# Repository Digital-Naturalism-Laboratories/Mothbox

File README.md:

# Mothbox
Developing an open source,low cost automated system for Moth-Lighting photography 

look at the wiki for up to date information on assembly and usage
https://github.com/Digital-Naturalism-Laboratories/Mothbox/wiki

It's a compact, low cost device you can get running with simple modifications of off-the-shelf parts! And no soldering really needed!

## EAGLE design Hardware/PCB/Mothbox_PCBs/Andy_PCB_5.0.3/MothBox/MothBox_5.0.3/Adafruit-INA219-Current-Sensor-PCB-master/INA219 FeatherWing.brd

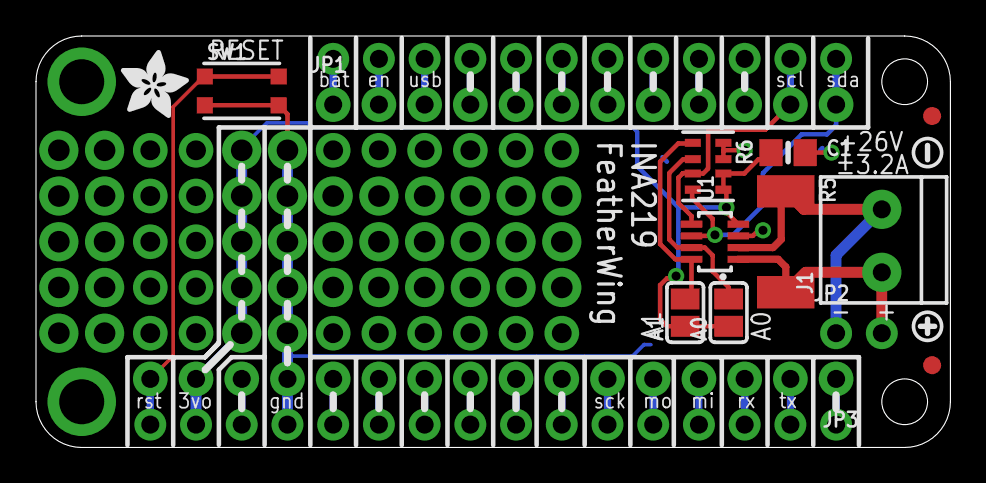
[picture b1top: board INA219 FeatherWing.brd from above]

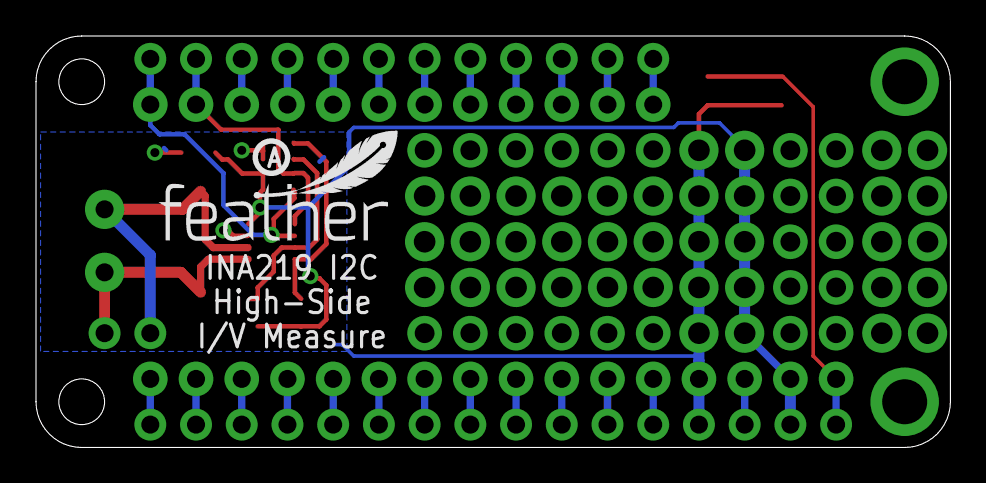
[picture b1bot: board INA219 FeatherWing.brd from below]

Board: 2 copper layers, 50.8 x 22.9 mm, 19 parts (2 on the bottom side), 32 nets.

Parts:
A0, A1: SOLDERJUMPER_REFLOW_NOPASTE
C1: 1uF; 0805-NO@1
FID1, FID2: FIDUCIAL_1MM
J1: 3.5mm; TERMBLOCK_1X2-3.5MM
JP1: 1X12_ROUND_76MIL
JP2: 1X02_ROUND
JP3: 1X16_ROUND_76MIL
MS1: FEATHERWING
R5: 0.1/1% (PT2512FK-070R1L); 2512
R6: 10K; RESPACK_4X0603
SW1: KMR2; BTN_KMR2_4.6X2.8
U1: INA219BIDCNT; SOT23-8
U$12: SYMBOL_PLUS
U$13: SYMBOL_MINUS
U$15: FEATHERLOGO_SMALL
U$16: ADAFRUIT_3.5MM
U$17: PCBFEAT-REV-040

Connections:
3.3V: A0.1, A1.1, C1.1, JP3.15, MS1.2, R6.5, R6.6, U1.4
A: JP3.12, MS1.5
AREF: JP3.14, MS1.3
B: JP3.11, MS1.6
C: JP3.10, MS1.7
D: JP3.9, MS1.8
E: JP3.8, MS1.9
EN: JP1.2, MS1.27
F: JP3.7, MS1.10
G: JP3.1, MS1.16
GND: C1.2, JP3.13, MS1.4, R6.7, R6.8, SW1.B, SW1.B', U1.3
H: JP1.10, MS1.19
I: JP1.9, MS1.20
J: JP1.8, MS1.21
K: JP1.7, MS1.22
L: JP1.6, MS1.23
M: JP1.5, MS1.24
MISO: JP3.4, MS1.13
MOSI: JP3.5, MS1.12
N: JP1.4, MS1.25
unnamed: A1.2, R6.1, U1.8
unnamed: A0.2, R6.2, U1.7
RESET: JP3.16, MS1.1, SW1.A, SW1.A'
RX: JP3.3, MS1.14
SCK: JP3.6, MS1.11
SCL: JP1.11, MS1.18, R6.3, U1.5
SDA: JP1.12, MS1.17, R6.4, U1.6
TX: JP3.2, MS1.15
USB: JP1.3, MS1.26
VBAT: JP1.1, MS1.28
VIN+: J1.2, JP2.2, R5.2, U1.1
VIN-: J1.1, JP2.1, R5.1, U1.2

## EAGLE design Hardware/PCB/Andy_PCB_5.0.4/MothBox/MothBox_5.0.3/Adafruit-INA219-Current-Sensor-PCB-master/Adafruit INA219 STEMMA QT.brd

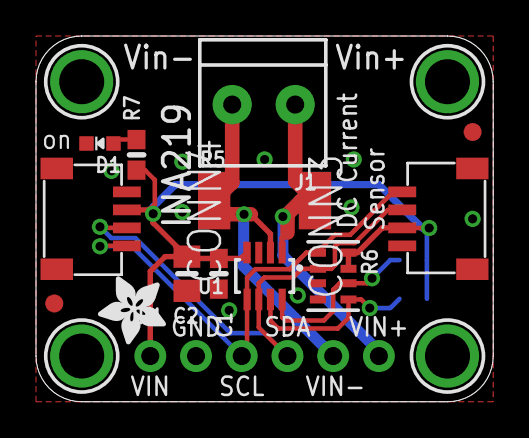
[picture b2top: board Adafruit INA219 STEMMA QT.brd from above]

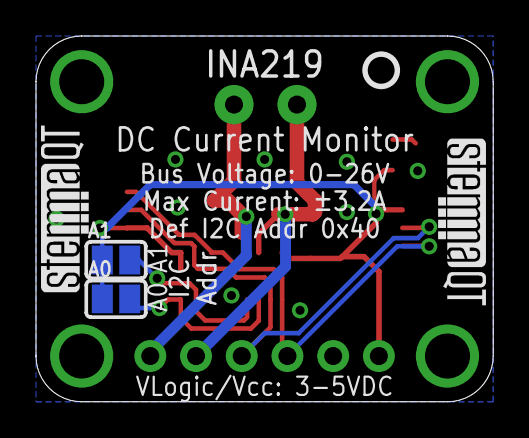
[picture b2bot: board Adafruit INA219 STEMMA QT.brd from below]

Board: 2 copper layers, 25.4 x 20.3 mm, 23 parts (5 on the bottom side), 9 nets.

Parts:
A0, A1: SOLDERJUMPER_REFLOW_NOPASTE
C1: 0.1µF; 0603-NO
C2: 10uF; 0805-NO
CONN3, CONN4: STEMMA_I2C_QT; JST_SH4
D1: GREEN; CHIPLED_0603_NOOUTLINE
FID3, FID4: FIDUCIAL_1MM
J1: 3.5mm; TERMBLOCK_1X2-3.5MM
JP1: 1X06_ROUND_70
R5: 0.1/1% (PT2512FK-070R1L); 2512
R6: 10K; RESPACK_4X0603
R7: 10K; 0603-NO
U1: INA219BIDCNT; SOT23-8
U$20, U$21, U$25, U$27: MOUNTINGHOLE2.5; MOUNTINGHOLE_2.5_PLATED
U$29: ADAFRUIT_3.5MM
U$30: PCBFEAT-REV-040
U$31, U$32: STEMMAQT

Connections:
ADDR0: A0.2, R6.5, U1.7
ADDR1: A1.2, R6.6, U1.8
GND: C1.2, C2.2, CONN3.1, CONN3.MT1, CONN3.MT2, CONN4.1, CONN4.MT1, CONN4.MT2, D1.C, JP1.2, R6.3, R6.4, U1.3
unnamed: D1.A, R7.2
SCL: CONN3.4, CONN4.4, JP1.3, R6.1, U1.5
SDA: CONN3.3, CONN4.3, JP1.4, R6.2, U1.6
VCC: A0.1, A1.1, C1.1, C2.1, CONN3.2, CONN4.2, JP1.1, R6.7, R6.8, R7.1, U1.4
VIN+: J1.2, JP1.6, R5.2, U1.1
VIN-: J1.1, JP1.5, R5.1, U1.2

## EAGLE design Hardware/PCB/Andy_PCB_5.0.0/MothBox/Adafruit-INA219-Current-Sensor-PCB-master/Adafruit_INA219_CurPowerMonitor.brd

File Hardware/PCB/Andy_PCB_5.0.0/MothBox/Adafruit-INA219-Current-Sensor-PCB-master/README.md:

## Adafruit INA219 Current Sensor PCB

<a href="http://www.adafruit.com/products/904"><br/>
Click here to purchase one from the Adafruit shop</a>
<a href="http://www.adafruit.com/products/3650"><br/>
Click here to purchase one from the Adafruit shop</a>

PCB files for the Adafruit INA219 Current Sensor. 

Format is EagleCAD schematic and board layout
* https://www.adafruit.com/product/904
* https://www.adafruit.com/product/3650

### Description

The INA219 will solve all your power-monitoring problems. Instead of struggling with two multimeters, you can just use the handy INA219B chip to both measure both the high side voltage and DC current draw over I2C with 1% precision.

Most current-measuring devices such as our current panel meter are only good for low side measuring. That means that unless you want to get a battery involved, you have to stick the measurement resistor between the target ground and true ground. This can cause problems with circuits since electronics tend to not like it when the ground references change and move with varying current draw. This chip is much smarter - it can handle high side current measuring, up to +26VDC, even though it is powered with 3 or 5V. It will also report back that high side voltage, which is great for tracking battery life or solar panels.

A precision amplifier measures the voltage across the 0.1 ohm, 1% sense resistor. Since the amplifier maximum input difference is ±320mV this means it can measure up to ±3.2 Amps. With the internal 12 bit ADC, the resolution at ±3.2A range is 0.8mA. With the internal gain set at the minimum of div8, the max current is ±400mA and the resolution is 0.1mA. Advanced hackers can remove the 0.1 ohm current sense resistor and replace it with their own to change the range (say a 0.01 ohm to measure up 32 Amps with a resolution of 8mA)

### License

Adafruit invests time and resources providing this open source design, please support Adafruit and open-source hardware by purchasing products from [Adafruit](https://www.adafruit.com)!

Designed by Limor Fried/Ladyada for Adafruit Industries.

Creative Commons Attribution/Share-Alike, all text above must be included in any redistribution. 
See license.txt for additional details.

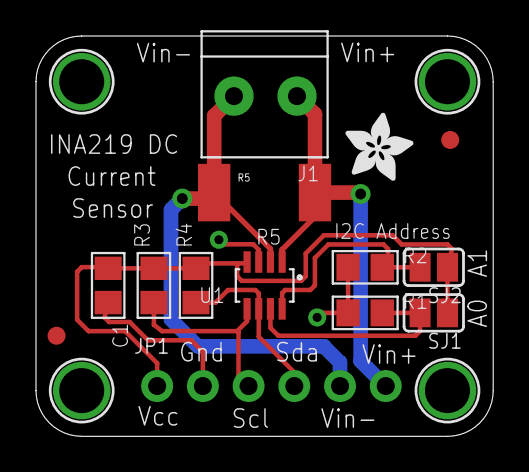
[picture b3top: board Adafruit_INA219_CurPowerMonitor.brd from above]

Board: 2 copper layers, 25.4 x 22.2 mm, 18 parts (0 on the bottom side), 8 nets.

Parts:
C1: 0.1µF; 0805
FID1, FID2: FIDUCIAL""; FIDUCIAL_1MM
J1: TERMBLOCK_1X2-3.5MM; 1X2-3.5MM
JP1: 1X06_ROUND_70
R1, R2, R3, R4: 10K; 0805
R5: 0.1/1% (PT2512FK-070R1L); 2512
SJ1, SJ2: SOLDERJUMPER_REFLOW_NOPASTE
U1: INA219BIDCNT; SOT23-8
U$7, U$8, U$9, U$10: MOUNTINGHOLE2.5; MOUNTINGHOLE_2.5_PLATED
U$11: ADAFRUIT_3.5MM

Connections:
GND: C1.2, JP1.2, R1.1, R2.1, U1.3
unnamed: R2.2, SJ2.2, U1.8
unnamed: R1.2, SJ1.2, U1.7
SCL: JP1.3, R3.1, U1.5
SDA: JP1.4, R4.1, U1.6
VCC: C1.1, JP1.1, R3.2, R4.2, SJ1.1, SJ2.1, U1.4
VIN+: J1.2, JP1.6, R5.2, U1.1
VIN-: J1.1, JP1.5, R5.1, U1.2

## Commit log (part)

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2025-11-27 Had to swap SW2 for a SMD version
2025-12-04 Add BeetlePalooza-related links
    include Imageomics URL and Bucket of Bugs project repo
2025-12-16 organizing site
2025-12-16 External parts
2025-12-16 fix names
2025-12-17 Define styles for navigation list levels
    Added styles for nested navigation levels.
2025-12-17 Update custom.scss with active link style
    Commented out font-weight property and added active link background style.
2025-12-17 Fix SCSS syntax and update background properties
2025-12-17 Update nav-list-link selector to use anchor tag
2025-12-17 Add width property to Level 2 nav-list links
2025-12-17 Adjust margin-left for nav-list links
    Updated margin-left for nav-list links from 1rem to 2rem.
2025-12-20 Organizing Case Options
2025-12-23 v5.0.4 schematic and PCB done. Ready for review
2025-12-24 flushing old versions
2025-12-26 renamed 24v areas to be actually 9-36v areas
2025-12-26 update kicad
2025-12-27 updated 5.x case stuff with rubber ties
2025-12-28 MADE UV m3 holes ready for JLCPCB
2025-12-29 updated footprints of d1 d2 d4 to SOD 123
2026-01-06 new Display for 4.x
    Refactor GPIO connection checks and update display logic. Added mode descriptions and improved voltage percentage calculation.
2026-01-06 Update controls.txt with new configuration values
2026-01-06 Add photo counting and update display info
2026-01-06 4.16.4 stuff
2026-01-07 Refactor shutdown process and remove GPS check
    Removed unnecessary GPS check at shutdown and updated shutdown procedure for Raspberry Pi 5.
2026-01-08 better battery values
2026-01-08 new 4.5 version cached
2026-01-08 Enhance Mothbox section with links and fixes
    Updated Mothbox descriptions with links and corrected typos.
2026-01-08 Add PCB attachment instructions to assembleincase.md
    Added instructions for attaching the PCB to the chassis with images.
2026-01-08 Add image to case_print.md
    Added an image of the 3D printable case for Mothbox.
2026-01-08 Enhance case_print.md with printing and assembly details
    Added detailed printing instructions and material list for case parts.
2026-01-09 Refactor Mothbox display logic and mode handling
    Updated mode handling and display information for Mothbox. Enhanced font usage and improved external drive information display.
2026-01-10 Adjust font sizes and layout in UpdateDisplay.py
2026-01-10 Refactor Mothbox display logic and font styles
    Refactor Mothbox display code to improve readability and update font styles. Adjusted control value retrieval and display elements for better clarity.
2026-01-13 getting rid of Pijuice only, turn everything off scripts
2026-01-17 Document Mothbeam connection setup and configuration
    Added detailed instructions for connecting Mothbeams to the mainboard, including configuration options and reinforcement tips.
2026-01-17 Update parts list for Mothbox Pro build
    Added detailed list of parts required to build a Mothbox Pro, including descriptions and prices.
2026-01-17 Update Mothbox Pro parts documentation
    Added an image and updated parts list for Mothbox Pro.
2026-01-18 added lip to front lid to hold it on better!
2026-01-19 made plug for box holes
2026-01-20 Update battery.md with regulator connection details
    Added instructions for connecting the regulator and battery power to the board.
2026-01-20 Update battery.md with setup instructions and notes
    Added notes on battery charging and Mothbox setup.
2026-01-20 Update assembly instructions for Mothbox Pro
    Added instructions for housing the Mothbox Pro and securing the PCB.
2026-01-20 Update case assembly instructions and component list
    Added DC barrel sockets to the list of components and clarified gasket usage for the back lid. Updated assembly instructions for the front acrylic and back lid.
2026-01-21 Update arms.md with assembly instructions
    Added sections on peeling plastic and attaching arms with various methods.
2026-01-22 code from 4.16.5
2026-01-22 MB Pro Scripts
2026-01-30 pro 5.1.0 firmware
2026-01-30 Finished fixing up Firmware for 4.17.0
2026-02-02 4.17.0 image files
2026-02-05 Fix broken link in processingsoftware.md
2026-02-05 Fix two broken links in cluster.md
2026-02-06 Clarify weekday and hour configuration in CSV
    Updated weekday and hour settings for clarity.
2026-02-07 Enhance battery.md with assembly and setup notes
    Added notes for battery assembly and setup steps.
2026-02-07 Expand timezone list with additional entries
    Added numerous time zones to the timezone list, expanding coverage for various regions.
2026-02-07 Revise time setting instructions for mothbox
    Updated the section on setting the time for the mothbox, including instructions for both manual and automatic time settings. Added images and clarified the process for users without internet access.
2026-02-07 Add optional custom mothbox name setup instructions
    Added instructions for setting a custom mothbox name.
2026-02-07 Update test.md with testing and battery info
    Added testing instructions and battery connection warnings.
2026-02-07 moved solar info
2026-02-07 Update get_utc_offset_hours to return rounded float
    Change return type of UTC offset to rounded float for fractional timezones.
2026-02-07 Update devblog with February 2026 entry
    Added a new entry detailing preparations for mothboxes and a bug fix related to fractional timezones.
2026-02-07 updated 5.1.1 mb image
2026-02-08 Fixed scheduling bug in 5.1.1 and 4.17.1
2026-02-08 Document Mothbox modes and settings
    Added detailed descriptions of Mothbox modes and how to set them for both DIY and Pro versions.
2026-02-08 latest case designs
2026-02-11 Fix typo in initialsetup.md
2026-02-12 fixed regex in detect as well
2026-02-12 Replace old image with new Mothbox Pro image
2026-02-12 Add connectors section to parts documentation
    Added section on connectors with options for securing the lid and legs.
2026-02-13 Update connect.md with Pi and camera connection details
    Added instructions for connecting the Pi and camera, including RTC battery installation and cable management.
2026-02-17 fixed regex
2026-02-17 Update nav_order for Classification documentation
2026-02-17 Update nav_order for Process documentation
2026-02-19 Revise project updates and add repository links
    Updated README to reflect project re-organization and added links to separate repositories.
2026-02-19 moved PCBS
2026-03-03 Add images to processing documentation
2026-03-17 Enhance instructions for connecting brown cable
    Added notes for connecting the brown cable to the camera.
2026-03-17 tweaks to forms examples
2026-03-17 scooting
2026-03-17 Update metadata logging and deployment instructions
    Revised instructions for metadata logging and Mothbox operation.
2026-03-17 Update usage instructions for Mothbox deployment
2026-03-18 Enhance battery charging and deployment instructions
    Added a warning about charging batteries before first use and improved instructions for preparing and deploying the Mothbox.
2026-03-18 Update databases.md with transition notice to Classify
    Added a note about the transition to the new Classify software.
2026-03-19 Update filament suggestions with outdoor usage notes
    Added a note about the suitability of regular PETG for outdoor equipment and cautioned against using PLA in tropical conditions.
2026-03-24 Update case_print.md with additional acrylic details
2026-03-24 Revise Mothbox DIY guide title and content
    Updated the title and added an introductory paragraph with an image for the Mothbox DIY guide.
2026-03-26 Remove FTP credentials from RemoveAccents_FTP.py
    Removed sensitive FTP credentials from the script.
2026-03-27 Update parts.md with download links for components
    Added download links for 3D printed and laser cut parts in the Mothbox Pro documentation.
2026-03-30 Enhance Mothbox description for deployment options
    Updated description to clarify deployment options for Mothbox.
2026-03-31 Update manufacture.md with purchasing options
    Added information about purchasing pre-made Mothbox Pro PCBs and updated various sections for clarity.
2026-03-31 Enhance BOM processing instructions in manufacture.md
    Added detailed instructions for processing the Bill of Materials (BOM) and handling common errors during PCB manufacturing.
2026-04-01 Clarify Mothbox modes descriptions
    Updated descriptions for Mothbox modes to clarify functionality and power states.
2026-04-01 reorg pages
2026-04-02 Add screws section to parts documentation
    Added a section for screws with specifications.
2026-04-02 Fix link for Talentcell PB120B1 battery
    Updated the link for the Talentcell PB120B1 battery to point to Walmart.
2026-04-18 Update processing documentation with usage options
    Added options for using the processing software with links.
2026-04-18 Update software download link to latest release
    Updated the link to the latest release for better accessibility.
2026-04-19 Revise mailing list and order form details
    Updated the mailing list and order form sections for clarity.
2026-04-19 update organization
2026-04-22 Update Mothbox documentation with pricing details
    Added pricing information for Mothbox Pro and DIY versions.
2026-04-28 Update manufacture.md with additional PCB links
    Added links to Mothbox PCB and Mothbeam PCBs for easier access.
2026-05-01 Update parts list with new components
    Added Lever Nut as a new component and clarified the optional Epaper Display.
2026-05-10 Revise README with updated repository links
    Updated links for Post-Processing and reorganized repository information.
2026-05-10 Update installation instructions for Windows and MacOS
    Added installation instructions for Windows and MacOS, including steps to bypass security settings on MacOS.
2026-05-12 Document bootloader flashing process for Raspberry Pi
    Added instructions for flashing a special bootloader on Raspberry Pi to resolve boot issues.
2026-05-15 Enhance troubleshooting documentation for Mothbox
    Updated troubleshooting guide for Mothbox with additional details and formatting improvements.
2026-05-15 Add publications section to about page
    Added a section for publications related to the Mothbox project, including links to papers and preprints.
2026-05-17 Revise specs for cost, runtime, and microcontroller
    Updated runtime specifications and added microcontroller details.
2026-06-03 Add link to scientific paper on Mothbox
    Added a link to a scientific paper about Mothbox usage.
2026-06-15 Enhance documentation for Windows and Mac setup
    Added instructions for activating virtual environments on Windows and Mac, including notes on running scripts in Visual Studio.
2026-06-18 Organizing the Organizing data with new structure
2026-06-21 Include zip tie hack for screw hole issues
    Added a zip tie hack section for securing components in the mothbox.
2026-06-24 Update collect_yolo_training_data.py
    made it work for obb files
2026-06-27 Can make patches for inspection before training
2026-06-28 ignored stuff
